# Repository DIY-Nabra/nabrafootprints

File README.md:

DIY-Nabra KiCAD footprint library
=================================

Peter Blasser makes beautiful and esoteric electronic instruments under the 
[Ciat-Lonbarde](https://www.ciat-lonbarde.net/ciat-lonbarde/index.html) brand name.

He has also published a series of DIY circuits intended to be built on a paper and 
cardboard sandwich called a paper circuit.  A summary of his paper circuits can be
found [here](https://www.ciat-lonbarde.net/ciat-lonbarde/TIMARACURRICULUM/TIMARATERIALS/cirques/index.html).
They contain an assortment of almost hieroglyphic like symbols which, coupled
with their non-orthogonal layouts, produce circuits that are artworks in themselves.

The majority of these paper circuits can be downloaded in a combined zip file from
[here](https://www.ciat-lonbarde.net/ciat-lonbarde/TIMARACURRICULUM/TIMARATERIALS/cirques/papers.zip).
The files in the zip are in the [Osmond PCB](https://www.osmondpcb.com) file format,
a Mac only application that is rather old and not supported on newer Macs, or Windows.

Ciat-Lonbarde DIY has a sizeable and enthusiastic on-line fanbase who have transferred
the paper circuits to PCBs, to make them easier to build.  Others have expanded on
the original circuits, or made their own circuits inspired by Peter's works.  The
unorthodox, yet aesthetic, symbols and layout of the circuits also has their 
admirers and a number of synth DIY enthusiasts have laid out their own circuits in
a manner similar to Peter's.

To encourage and support these enthusiasts and, mainly, as I am one of them, I spent
a typically UK winter wet Sunday afternoon writing a Python script to convert the 
component footprint symbols used in the Osmond PCB versions of the Ciat-Lonbarde 
paper circuits to [KiCAD](https://www.kicad.org) footprint symbols.  This repository is 
the product of that afternoon.  It contains:

* The KiCAD footprint library: `diy-nabra.pretty`
* The Python conversion script I wrote: `conversion-script/osm-to-kicad.py`
* The Osmond PCB footprint library I exported from Osmond PCB: `conversion-script/cl_osmond_library.osm`
* An example KiCAD project using the footprints: `3-roll/3-roll.kicad_pro`.  
This is a recreation of the 3-Roll circuit from Rollz-5 in KiCAD.  I have laid it 
out starting with the schematic.  I choose this as it is the simplest of all 
the paper circuits.
* A KiCAD project with all the footprints that I used to generate the image below:

How to use
----------

* Clone the repo from GitHub: ```git clone https://github.com/DIY-Nabra/NabraFootprints.git```
    * or download the zipfile from: [```https://github.com/DIY-Nabra/NabraFootprints/archive/refs/tags/1.0.0.zip```](https://github.com/DIY-Nabra/NabraFootprints/archive/refs/tags/1.0.0.zip)
* In the KiCAD PCB editor (`pcbnew`) go to `Preferences->Manage Footprint Libraries...`
    * Click the folder icon beneath the list of footprint libraries to add a new library from a directory
    * Navigate to the `diy-nabra.pretty` directory in the `NabraFootprints` directory that you cloned or expanded the zipfile into.
    * Click `Open`
* You should now see the `diy-nabra` Nickname and path in the list of footprints.

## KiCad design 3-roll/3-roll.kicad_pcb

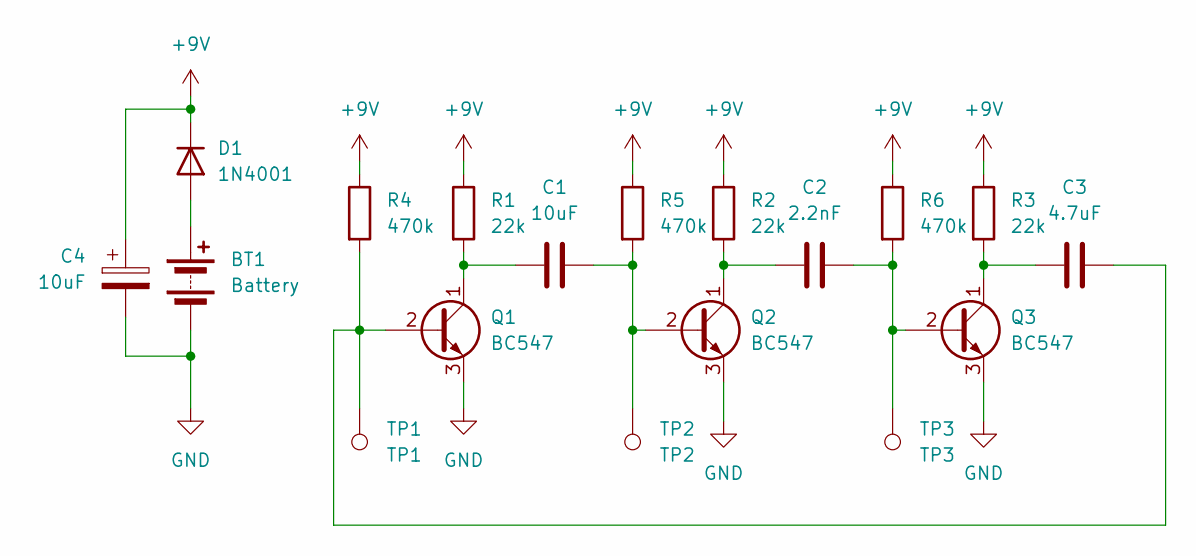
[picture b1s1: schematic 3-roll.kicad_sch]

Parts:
BT1: Battery; wobelisk
C1: 10uF; chairy
C2: 2.2nF; chairy
C3: 4.7uF; chairy
C4: 10uF; cel1
D1: 1N4001; do3
Q1, Q2, Q3: BC547; qnpn
R1, R2, R3: 22k; r3
R4, R5, R6: 470k; r3
TP1: TP1; wsqout
TP2: TP2; wsqout
TP3: TP3; wsqout

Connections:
+9V: C4.1, D1.1 (K), R1.1, R2.1, R3.1, R4.1, R5.1, R6.1
GND: BT1.2 (-), C4.2, Q1.3 (E), Q2.3 (E), Q3.3 (E)
unnamed: BT1.1 (+), D1.2 (A)
unnamed: C3.2, Q1.2 (B), R4.2, TP1.1
unnamed: C1.1, Q1.1 (C), R1.2
unnamed: C1.2, Q2.2 (B), R5.2, TP2.1
unnamed: C2.1, Q2.1 (C), R2.2
unnamed: C2.2, Q3.2 (B), R6.2, TP3.1
unnamed: C3.1, Q3.1 (C), R3.2

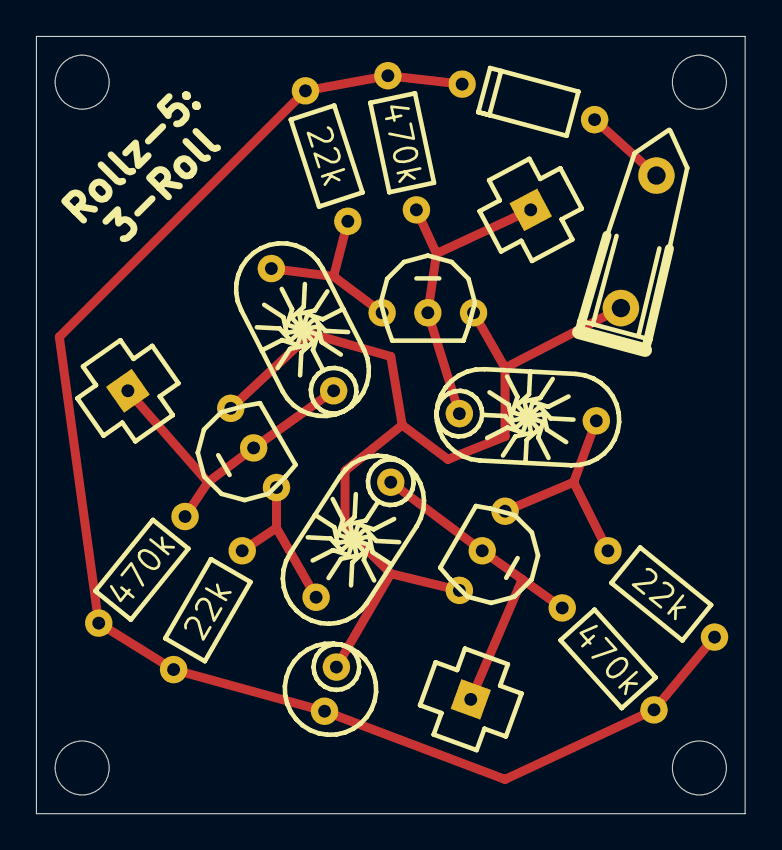
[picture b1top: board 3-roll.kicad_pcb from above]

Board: 2 copper layers, 39.4 x 43.2 mm, 18 parts (0 on the bottom side), 9 nets.

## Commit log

2025-02-04 First release
2025-02-10 Corrected LED footprints
2025-04-15 The international language of square pads
